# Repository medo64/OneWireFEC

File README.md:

1-Wire Framework Expansion Card
===============================

Non-isolated 1-Wire master.

## Pinout

To connect to this board, one has to use a 3-pin JST XH connector. The following
table represents the pinout, pin 1 being on the left as looking into the
expansion card.

| # | Ref   | Description                     |
|--:|:-----:|---------------------------------|
| 1 | GND   | Ground connection               |
| 2 | DQ    | Data                            |
| 3 | V+    | Positive voltage                |

Output voltage is either 3.3V or 5V at up to 100 mA.

## LEDs

Left LED signals if serial data is received or sent.

Right LED signals if output is active and there is no fault.

---
*You can check my blog and other projects at [www.medo64.com](https://www.medo64.com/electronics/).*

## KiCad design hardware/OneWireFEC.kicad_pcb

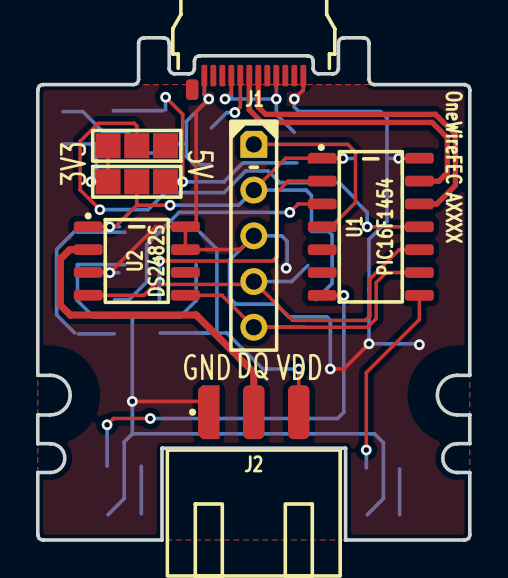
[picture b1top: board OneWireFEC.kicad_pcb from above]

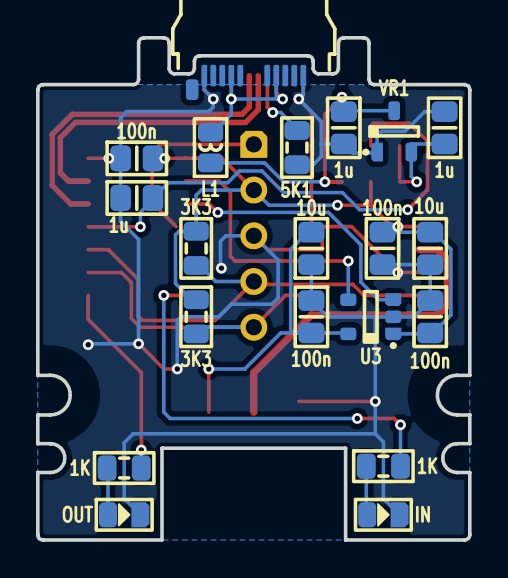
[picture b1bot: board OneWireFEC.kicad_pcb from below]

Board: 2 copper layers, 24.0 x 27.9 mm, 26 parts (19 on the bottom side), 20 nets.

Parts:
C1, C2, C3, C4: 100n; C (0805)
C5, C6, C7: 1u; C (0805)
C8, C9: 10u; C (0805)
DS1: IN; DS (0805)
DS2: OUT; DS (0805)
ICSP: Microchip PIC; ICSP PIC Pogo (5w)
J1: 105444-0001; J USB C 3.2 Edge (24w)
J2: B2B-XH-A; J JST XH Edge [1WIRE] (3w)
JP1, JP2: Jumper; JP Dual (1205)
L1: 120R; L (0805)
R1, R2: 1K; R (0805)
R3, R4: 3K3; R (0805)
R5: 5K1; R (0805)
U1: PIC16F1454; U Micro [PIC16F1454] (SOIC-14)
U2: DS2482S; U Transceiver 1Wire [DS2482S-100+] (SOIC-8)
U3: MIC2091; U LoadSwitch 100mA [MIC2091-1] (SOT23-5)
VR1: MCP1700; VR Linear 3.3V 250mA [MCP1700] (SOT-23)

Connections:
3V3: C7.2, JP1.1, JP2.3, VR1.2
3V3_USB: C5.1, JP2.2, U1.11
5V: C6.2, JP1.3, L1.2, VR1.3
A_CC: J1.A5, R5.2
DQ: J2.2, U2.2
GND: C1.2, C2.1, C3.2, C4.2, C5.2, C6.1, C7.1, C8.2, C9.2, DS1.1, DS2.1, ICSP.3, J1.A1, J1.A12, J1.B01, J1.B12, J2.1, R5.1, U1.14, U2.3, U2.7, U2.8, U3.2, VR1.1
ICSP_VPP: ICSP.1, U1.4
LED_A: R1.1, U1.7
LED_A': DS1.2, R1.2
LED_B: R2.1, U1.8
LED_B': DS2.2, R2.2
POWER_EN: U1.3, U3.3
POWER_FAULT: U1.2, U3.4
SCL: ICSP.4, R3.1, U1.10, U2.4
SDA: ICSP.5, R4.1, U1.9, U2.5
USB_DM: J1.A7, U1.12
USB_DP: J1.A6, U1.13
VDD: C1.1, C2.2, C3.1, C8.1, ICSP.2, JP1.2, R3.2, R4.2, U1.1, U2.1, U3.1
VDD_OUT: C4.1, C9.1, J2.3, U3.5
Vin: J1.A4, J1.A9, J1.B04, J1.B09, L1.1

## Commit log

2024-02-19 Initial version
2024-02-19 Added pull-up resistors for I2C and added Vusb3V3 jumper
2024-02-20 Fixed a few typos
2024-04-02 Changed connector name
2024-04-18 Added output labels
2024-04-18 Refactoring
2024-05-01 Upgraded to KiCAD 8
2024-05-01 Adjusting solder-on jumpers to be more symetric
